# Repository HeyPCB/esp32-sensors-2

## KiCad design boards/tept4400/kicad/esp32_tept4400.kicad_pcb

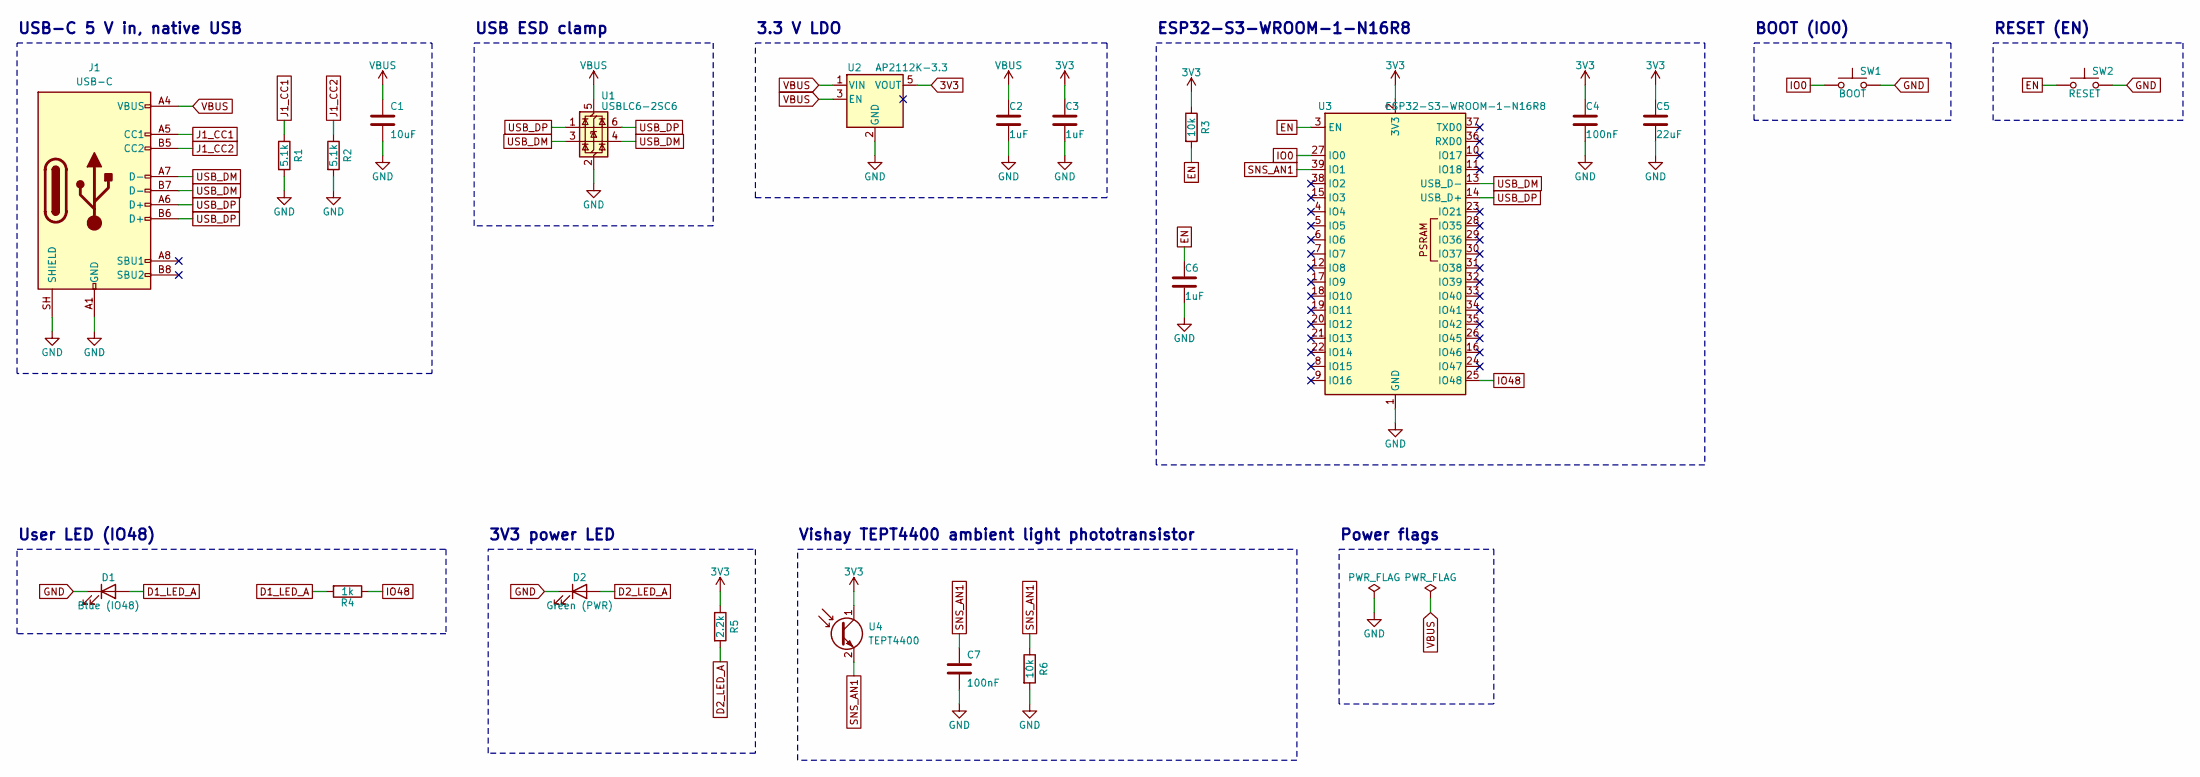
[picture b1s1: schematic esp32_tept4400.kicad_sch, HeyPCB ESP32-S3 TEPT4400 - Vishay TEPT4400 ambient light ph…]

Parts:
C1: 10uF; C_0805_2012Metric; MPN CL21A106KAYNNNE; LCSC C15850
C2, C3, C6: 1uF; C_0603_1608Metric; MPN CL10A105KB8NNNC; LCSC C15849
C4: 100nF; C_0603_1608Metric; MPN CC0603KRX7R9BB104; LCSC C14663
C5: 22uF; C_0805_2012Metric; MPN CL21A226MAQNNNE; LCSC C45783
C7: 100nF; C_0402_1005Metric; MPN CL05B104KO5NNNC; LCSC C1525
D1: Blue (IO48); LED_0603_1608Metric; MPN NCD0603B1; LCSC C84266
D2: Green (PWR); LED_0603_1608Metric; MPN KT-0603G; LCSC C12624
J1: USB-C; USB_C_Receptacle_HRO_TYPE-C-31-M-12; MPN TYPE-C-31-M-12; LCSC C165948
R1, R2: 5.1k; R_0402_1005Metric; MPN 0402WGF5101TCE; LCSC C25905
R3, R6: 10k; R_0603_1608Metric; MPN 0603WAF1002T5E; LCSC C25804
R4: 1k; R_0603_1608Metric; MPN 0603WAF1001T5E; LCSC C21190
R5: 2.2k; R_0603_1608Metric; MPN 0603WAF2201T5E; LCSC C4190
SW1: BOOT; SW_Push_1P1T_XKB_TS-1187A; MPN TS-1187A-B-A-B; LCSC C318884
SW2: RESET; SW_Push_1P1T_XKB_TS-1187A; MPN TS-1187A-B-A-B; LCSC C318884
U1: USBLC6-2SC6; SOT-23-6; MPN USBLC6-2SC6; LCSC C7519
U2: AP2112K-3.3; SOT-23-5; MPN AP2112K-3.3TRG1; LCSC C51118
U3: ESP32-S3-WROOM-1-N16R8; ESP32-S3-WROOM-1; MPN ESP32-S3-WROOM-1-N16R8; LCSC C2913202
U4: TEPT4400; LED_D3.0mm_Clear; MPN TEPT4400; LCSC C132178

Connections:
3V3: C3.1, C4.1, C5.1, R3.1, R5.1, U2.5 (VOUT), U3.2 (3V3), U4.1 (C)
D1_LED_A: D1.2 (A), R4.2
D2_LED_A: D2.2 (A), R5.2
EN: C6.1, R3.2, SW2.1, U3.3 (EN)
GND: C1.2, C2.2, C3.2, C4.2, C5.2, C6.2, C7.2, D1.1 (K), D2.1 (K), J1.A1 (GND), J1.A12 (GND), J1.B1 (GND), J1.B12 (GND), J1.SH (SHIELD), R1.2, R2.2, R6.2, SW1.2, SW2.2, U1.2 (GND), U2.2 (GND), U3.1 (GND), U3.40 (GND), U3.41 (GND)
IO0: SW1.1, U3.27 (IO0)
IO48: R4.1, U3.25 (IO48)
J1_CC1: J1.A5 (CC1), R1.1
J1_CC2: J1.B5 (CC2), R2.1
SNS_AN1: C7.1, R6.1, U3.39 (IO1), U4.2 (E)
USB_DM: J1.A7 (D-), J1.B7 (D-), U1.3 (I/O2), U1.4 (I/O2), U3.13 (USB_D-)
USB_DP: J1.A6 (D+), J1.B6 (D+), U1.1 (I/O1), U1.6 (I/O1), U3.14 (USB_D+)
VBUS: C1.1, C2.1, J1.A4 (VBUS), J1.A9 (VBUS), J1.B4 (VBUS), J1.B9 (VBUS), U1.5 (VBUS), U2.1 (VIN), U2.3 (EN)

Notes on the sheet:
USB-C 5 V in, native USB
USB ESD clamp
3.3 V LDO
ESP32-S3-WROOM-1-N16R8
BOOT (IO0)
RESET (EN)
User LED (IO48)
3V3 power LED
Vishay TEPT4400 ambient light phototransistor
Power flags

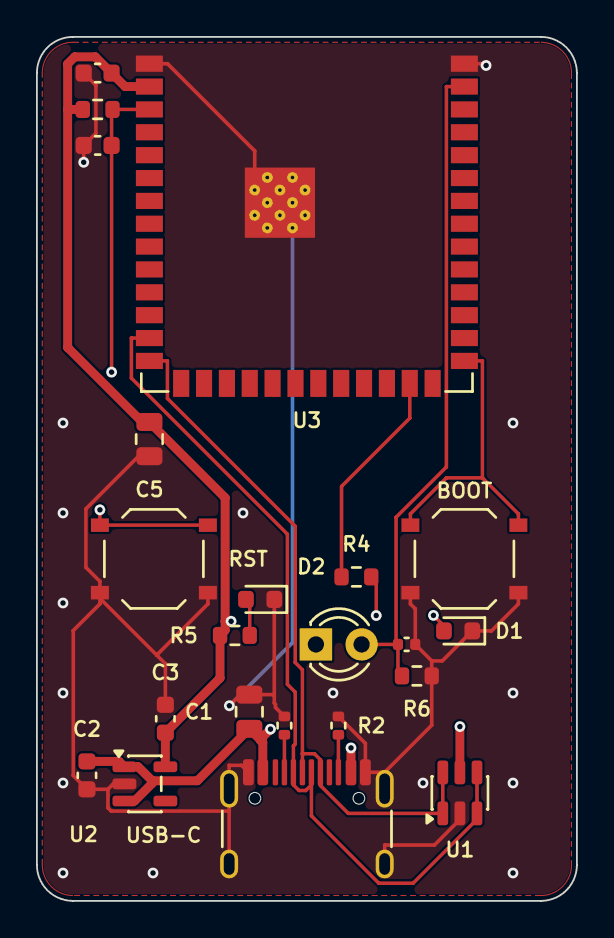
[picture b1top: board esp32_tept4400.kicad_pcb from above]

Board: 4 copper layers, 30.0 x 48.0 mm, 22 parts (0 on the bottom side), 13 nets.
